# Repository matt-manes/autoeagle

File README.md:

# Autoeagle

Automate tasks in Autodesk's Eagle software by invoking Python scripts from the program's command line.<br>

## Installation

Install with:

<pre>
pip install autoeagle
</pre>

## Setup

Before using Autoeagle, you should run the command line tool `autoeagle_config`.<br>
The tool's help display is:
<pre>
>autoeagle_config -h
usage: autoeagle_config [-h] [-e EAGLEDIR] [-u ULPDIR] [-s SCRIPTSDIR]

options:
  -h, --help            show this help message and exit
  -e EAGLEDIR, --eagledir EAGLEDIR
                        Path to user's Eagle directory. (Not the executable installation directory, but the one containing projects, libraries, ulps, etc.)
  -u ULPDIR, --ulpdir ULPDIR
                        Path to user's ulp directory. Only necessary if different from the standard ulp directory path.
  -s SCRIPTSDIR, --scriptsdir SCRIPTSDIR
                        Path to user's scripts directory. Only necessary if different from the standard scripts directory path.
</pre>

Standard Eagle installations should only need to provide the `-e/--eagledir` argument.

## Basic Usage
The basic workflow is to write a Python script that you would want to invoke from within Eagle,
then pass the path to the script as an argument to the included `generate_ulp` tool.<br>
This tool will create a ulp file named after your Python file.<br>
Then, inside Eagle, invoke it with the `run` command from the editor's command line like you would any other ulp.<br>
Because the ulp launches your Python file, you only need to use this tool for a script once unless
you move the Python file to a different location or start using the `ScriptWriter` class in the script when you didn't before.

There are three main components to use in this package: `autoeagle.core.Schematic`, `autoeagle.core.Board`, and `autoeagle.core.ScriptWriter`.<br>
The Schematic and Board classes are used to parse and manipulate the Eagle `.sch` and `.brd` xml files, respectively.<br>
The ScriptWriter class is used to generate `.scr` files that can be executed by Eagle when returning from the ulp invocation.<br>
<br>
When creating a Schematic or Board object, the file will be parsed during initialization.<br>
For example, all the parts used in the `dummy.sch` schematic (located in `autoeagle/tests/EAGLE/projects/dummy`) and their values can be printed out using
<pre>
>>> import autoeagle
>>> schem = autoeagle.core.Schematic("dummy.sch")
>>> parts = schem.get_attribute("name", schem.parts)
>>> values = schem.get_attribute("value", schem.parts)
>>> print(*[f"{part}: {value} for part,value in zip(parts,values)], sep="\n")
</pre>
The output:
<pre>
R1 1meg
R2 10k
R3 1meg
C1 1u
GND1 None
U$1 None
IC1 TL072
R4 100k
C2 100p
C3 100p
R5 10k
GND2 None
R6 10k
C4 1u
R7 100k
GND4 None
POWER None
GND5 None
GND6 None
V1 None
V2 None
V3 None
R8 10k
R9 10k
GND7 None
C5 10u
GND3 None
U$2 None
INPUT generic
GND8 None
OUTPUT generic
GND9 None
</pre>

<br>
When launching a Python script from Eagle with the generated ulp, the schematic or board file
will be passed to the Schematic or Board constructor without needing to be specified like the above example.<br>
<br>

## Walkthrough

In the 'sample_scripts' folder included with this package are some simple examples of how to use this package.<br>
We'll walk through the basics and the process with one of them.<br>
Create and open a file called `shrink_board.py`, then copy and paste the following:
<pre>
import autoeagle

def shrink_board(clearance: float):
    """Shrink board outline to be a given amount
    away from the outermost components.

    :param clearance: The minimum distance between
    the board edge and a component's center."""
    brd = autoeagle.core.Board()
    get_coordinates = lambda n: list(float(part.get(n)) for part in brd.parts)
    xs = get_coordinates("x")
    ys = get_coordinates("y")
    left = min(xs) - clearance
    right = max(xs) + clearance
    bottom = min(ys) - clearance
    top = max(ys) + clearance
    x0, xf, y0, yf = brd.get_bounds().values()
    
    with autoeagle.core.ScriptWriter() as scr:
        movements = [
            (x0, yf, left, top),
            (xf, yf, right, top),
            (xf, y0, right, bottom),
            (x0, y0, left, bottom),
        ]
        scr.display_layers(["Dimension"])
        for m in movements:
            scr += f"move ({m[0]} {m[1]}) ({m[2]} {m[3]})"
        scr.display_layers(brd.get_visible_layers())

if __name__ == "__main__":
    clearance = float(input("Enter minimum board clearance: "))
    shrink_board(clearance)

</pre>

This script will prompt the user for a clearance value, then
write a `.scr` file to move the board dimensions so that they are that amount
of distance away from the nearest component.<br>

Let's look closer at the `shrink_board` function.<br>
As mentioned earlier, the ulp file that invokes this script will pass the
`.brd` file path to the Board object for us, so we can instantiate it
with an empty constructor like `brd = autoeagle.core.Board()`.<br>

The next section
<pre>
get_coordinates = lambda n: list(float(part.get(n)) for part in brd.parts)
xs = get_coordinates("x")
ys = get_coordinates("y")
</pre>

iterates over the part elements and stores all the 'x' coordinates in 
one list and all the 'y' coordinates in another.

These lists are used, with the clearance value supplied by the user,
to determine the new board perimeter in the following lines:
<pre>
left = min(xs) - clearance
right = max(xs) + clearance
bottom = min(ys) - clearance
top = max(ys) + clearance
</pre>

Then we can obtain the current board perimeter with
<pre>
x0, xf, y0, yf = brd.get_bounds().values()
</pre>

`brd.get_bounds()` returns a dictionary so we can just use `.values()` to unpack values.

The final block of the function creates a ScriptWriter object.<br>
The ScriptWriter class is used to create a `.scr` file that can be run by Eagle.<br>
When generating the ulp file for our script, if it sees 'ScriptWriter' in the Python file,
it will tell Eagle to run the `.scr` file upon returning from the executing the ulp.<br>
Here's the ScriptWriter block:
<pre>
with autoeagle.core.ScriptWriter() as scr:
    movements = [
        (x0, yf, left, top),
        (xf, yf, right, top),
        (xf, y0, right, bottom),
        (x0, y0, left, bottom),
    ]
    scr.display_layers(["Dimension"])
    for m in movements:
        scr += f"move ({m[0]} {m[1]}) ({m[2]} {m[3]})"
    scr.display_layers(brd.get_visible_layers())
</pre>

The script this will write will first change the visible layers to only
show the 'Dimension' layer.<br>
It will then execute a series of four `move` commands.<br>
Each one will move a corner of the board from its current location to its new location,
as determined by the components and the user supplied clearance value.<br>
Finally, it will then reset the visible layers to whatever they were when the script was invoked.<br>
The `.scr` doesn't get generated until we invoke the ulp, but once we do, the generated script
will look something like the following:

<pre>
display none Dimension;
move (0.0 80.0) (-0.2999999999999998 25.7);
move (100.0 80.0) (19.9 25.7);
move (100.0 0.0) (19.9 0.04999999999999982);
move (0.0 0.0) (-0.2999999999999998 0.04999999999999982);
display none Top Bottom Pads Vias Dimension tPlace;
write;
</pre>

We didn't need to manually add the `write;` statement at the end,
because using the ScriptWriter class with a context manager will do that for us automatically.

Now that we've finished our script, it's time to generate the ulp.<br>
From the command line, navigate to the folder where you put the Python script we just wrote.<br>
Run the command `>generate_ulp shrink_board.py`.<br>
Now you should be able run the script in Eagle by entering `run shrink_board` in the editor's command line.<br>

To sum up, `run shrink_board` invokes the ulp file named `shrink_board.ulp` that was generated by the `generate_ulp` tool.<br>
That ulp then launches our Python script and passes the currently open file name to it.<br>
`shrink_board.py` parses the board file, prompts us for a minimum clearance, and generates a `.scr` file with the Eagle editor commands to 
appropriately shrink our board outline.<br>
Finally, upon exiting the ulp, it returns a command to Eagle to execute our new `.scr` file.
<br>

For further reference on editor commands that can be used in an `.scr` file, see the Eagle help documentation.

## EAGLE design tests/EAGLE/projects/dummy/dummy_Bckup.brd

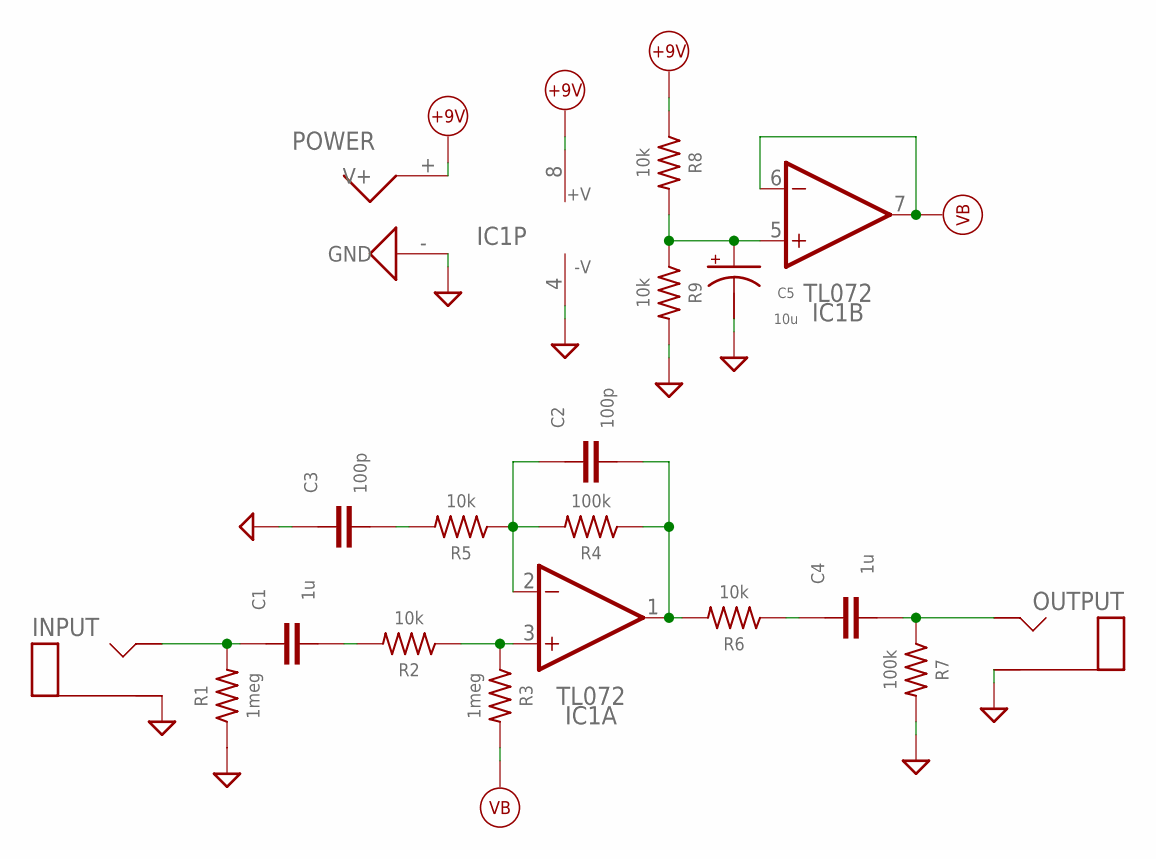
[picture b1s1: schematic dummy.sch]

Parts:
C1, C4: 1u; 0805
C2, C3: 100p; 0805
C5: 10u; 4X4.5SMD
IC1: TL072; SO08
INPUT: generic; TWO_PADS
OUTPUT: generic; TWO_PADS
POWER: POWERJACK_PADS; AB9V
R1, R3: 1meg; 0805
R2, R5, R6, R8, R9: 10k; 0805
R4, R7: 100k; 0805

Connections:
+9V: IC1.8 (VDD), POWER.+ (V+), R8.1
+VB: IC1.6 (-IN), IC1.7 (OUT), R3.2
GND: C3.1, C5.P$2 (-), IC1.4 (VSS), INPUT.S (SLEEVE), OUTPUT.S (SLEEVE), POWER.- (GND), R1.1, R7.2, R9.2
unnamed: C1.1, INPUT.T (TIP), R1.2
unnamed: C1.2, R2.2
unnamed: IC1.3 (+IN), R2.1, R3.1
unnamed: C2.2, IC1.1 (OUT), R4.1, R6.2
unnamed: C2.1, IC1.2 (-IN), R4.2, R5.1
unnamed: C3.2, R5.2
unnamed: C4.1, R6.1
unnamed: C4.2, OUTPUT.T (TIP), R7.1
unnamed: C5.P$1 (+), IC1.5 (+IN), R8.2, R9.1

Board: 2 copper layers, 18 parts (0 on the bottom side), 12 nets, no tracks yet.

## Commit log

2023-02-23 chore: build v1.0.0
2023-02-23 chore: update readme
2023-03-22 chore: build v1.0.1
